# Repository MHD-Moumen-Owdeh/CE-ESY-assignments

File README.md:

# README.md files related to the assignments are in the folders

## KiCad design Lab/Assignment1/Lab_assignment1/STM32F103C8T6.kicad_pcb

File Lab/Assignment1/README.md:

Here are the required files for the assignment.
I started working on the PCB design but wasn’t able to fully complete it before the deadline.
Any feedback or notes would be greatly appreciated.

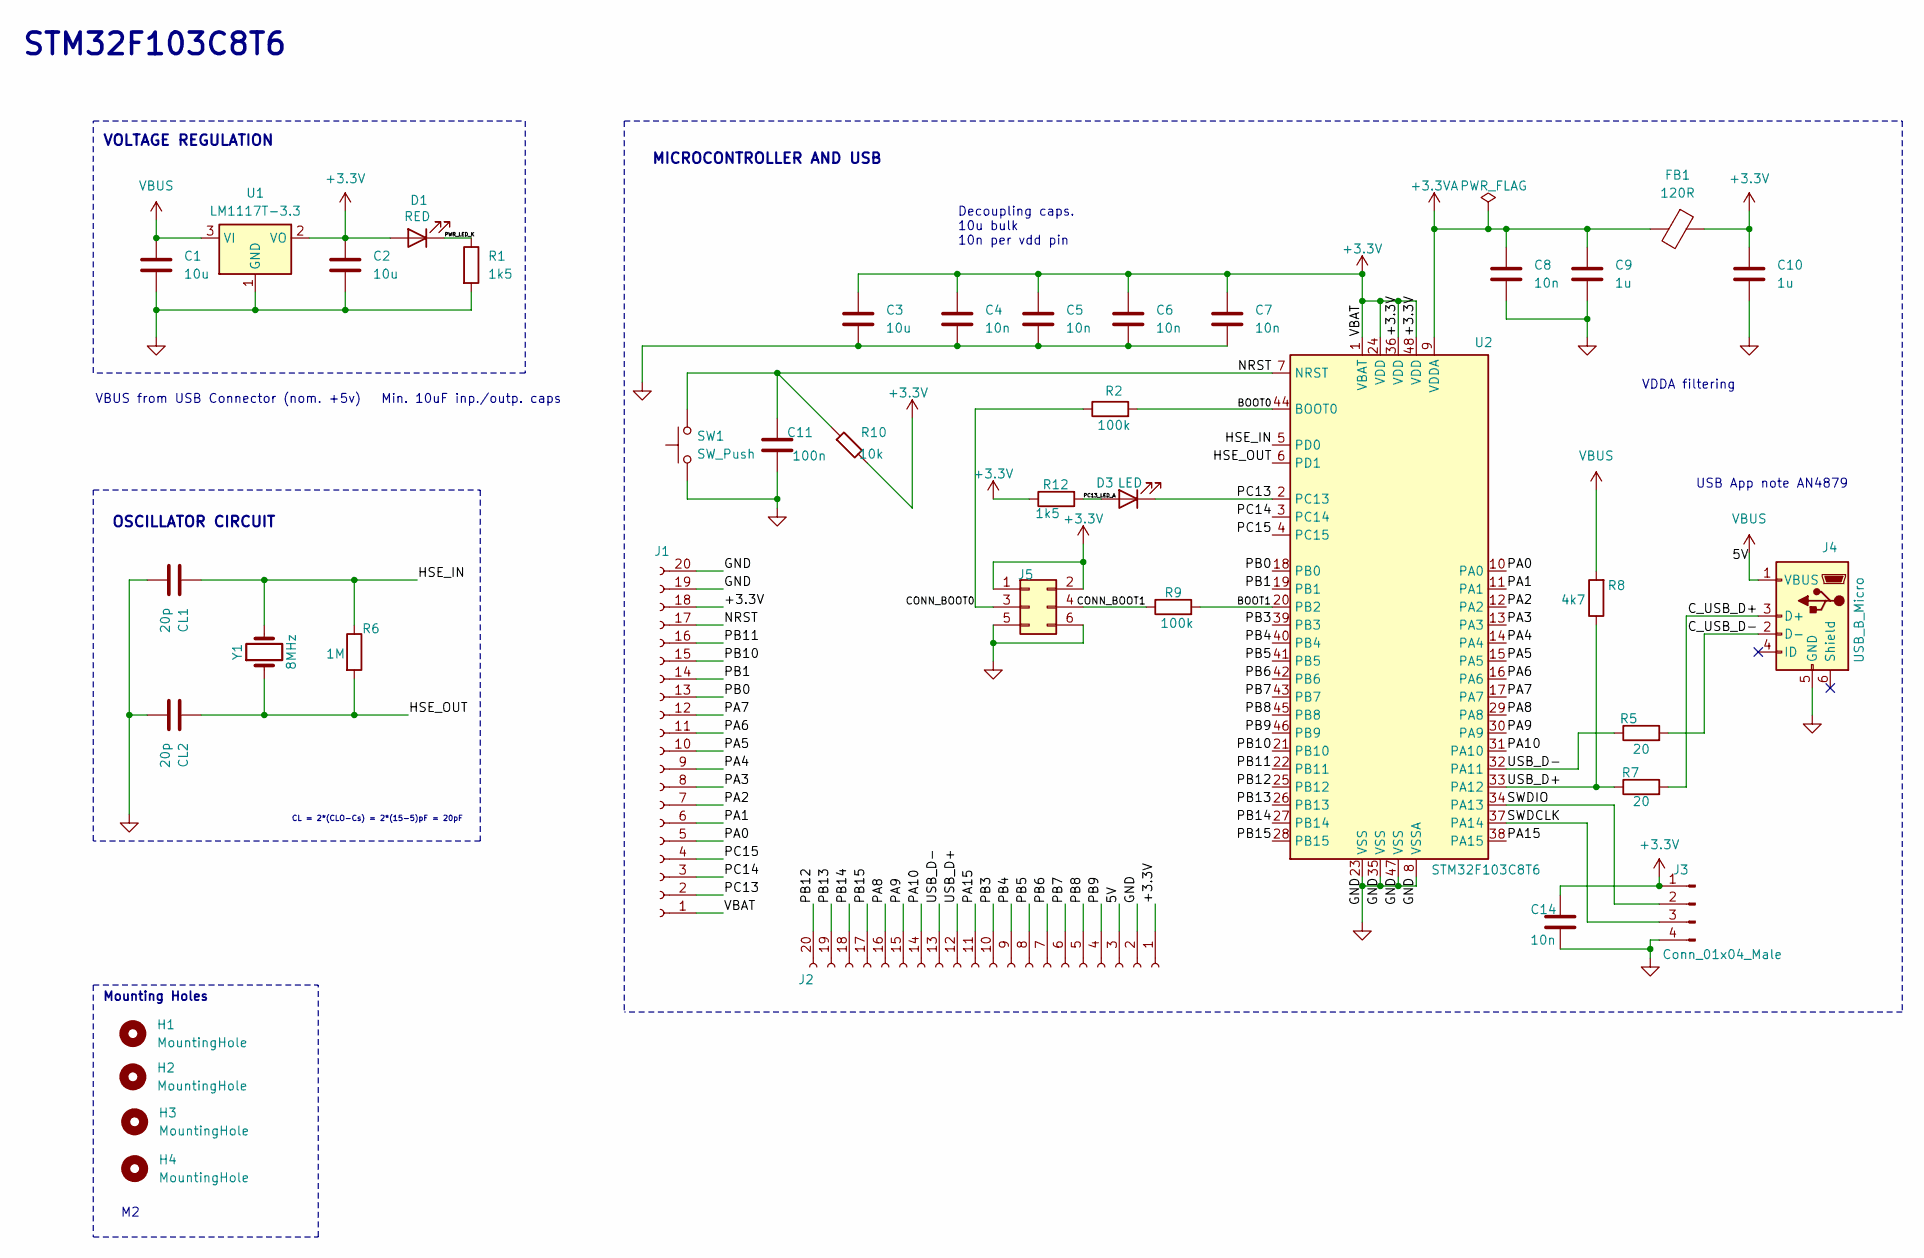
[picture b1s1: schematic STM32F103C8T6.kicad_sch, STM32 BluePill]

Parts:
C1, C2, C3: 10u; C_0603_1608Metric
C4, C5, C6, C7, C8: 10n; C_0603_1608Metric
C9, C10: 1u; C_0402_1005Metric
C11: 100n; C_0402_1005Metric
C14: 10n; C_0402_1005Metric
CL1, CL2: 20p; C_0402_1005Metric
D1: RED; LED_0603_1608Metric
D3: LED; LED_0603_1608Metric
FB1: 120R; L_0603_1608Metric
H1, H2, H3, H4: MountingHole; MountingHole_2.2mm_M2
J1, J2: Conn_01x20_Socket; PinSocket_1x20_P2.00mm_Vertical
J3: Conn_01x04_Male; PinHeader_1x04_P2.00mm_Vertical
J4: USB_B_Micro; USB_Micro-B_Wuerth_629105150521
J5: Conn_02x03_Odd_Even; PinHeader_2x03_P2.54mm_Vertical
R1, R12: 1k5; R_0402_1005Metric
R2, R9: 100k; R_0402_1005Metric
R5, R7: 20; R_01005_0402Metric
R6: 1M; R_0603_1608Metric
R8: 4k7; R_0402_1005Metric
R10: 10k; R_0402_1005Metric
SW1: SW_Push; SW_Push_1P1T_NO_CK_KMR2
U1: LM1117T-3.3; TO-220-3_Vertical
U2: STM32F103C8T6; LQFP-48_7x7mm_P0.5mm
Y1: 8MHz; Crystal_SMD_5032-2Pin_5.0x3.2mm_HandSoldering

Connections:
+3.3V: C2.1, C3.1, C4.1, C5.1, C6.1, C7.1, C10.1, C14.1, D1.2 (A), FB1.1, J1.1, J1.18, J2.1, J3.1, J5.1, J5.2, R10.2, R12.1, U1.2 (VO), U2.1 (VBAT), U2.24 (VDD), U2.36 (VDD), U2.48 (VDD)
+3.3VA: C8.1, C9.1, FB1.2, U2.9 (VDDA)
/BOOT0: R2.2, U2.44 (BOOT0)
/BOOT1: R9.2, U2.20 (PB2)
/CONN_BOOT0: J5.3, R2.1
/CONN_BOOT1: J5.4, R9.1
/C_USB_D+: J4.3 (D+), R7.2
/C_USB_D-: J4.2 (D-), R5.2
/HSE_IN: CL1.1, R6.1, U2.5 (PD0), Y1.2
/HSE_OUT: CL2.1, R6.2, U2.6 (PD1), Y1.1
/NRST: C11.1, J1.17, R10.1, SW1.2, U2.7 (NRST)
/PA0: J1.5, U2.10 (PA0)
/PA1: J1.6, U2.11 (PA1)
/PA2: J1.7, U2.12 (PA2)
/PA3: J1.8, U2.13 (PA3)
/PA4: J1.9, U2.14 (PA4)
/PA5: J1.10, U2.15 (PA5)
/PA6: J1.11, U2.16 (PA6)
/PA7: J1.12, U2.17 (PA7)
/PA8: J2.16, U2.29 (PA8)
/PA9: J2.15, U2.30 (PA9)
/PA10: J2.14, U2.31 (PA10)
/PA15: J2.11, U2.38 (PA15)
/PB0: J1.13, U2.18 (PB0)
/PB1: J1.14, U2.19 (PB1)
/PB3: J2.10, U2.39 (PB3)
/PB4: J2.9, U2.40 (PB4)
/PB5: J2.8, U2.41 (PB5)
/PB6: J2.7, U2.42 (PB6)
/PB7: J2.6, U2.43 (PB7)
/PB8: J2.5, U2.45 (PB8)
/PB9: J2.4, U2.46 (PB9)
/PB10: J1.15, U2.21 (PB10)
/PB11: J1.16, U2.22 (PB11)
/PB12: J2.20, U2.25 (PB12)
/PB13: J2.19, U2.26 (PB13)
/PB14: J2.18, U2.27 (PB14)
/PB15: J2.17, U2.28 (PB15)
/PC13: D3.1 (K), J1.2, U2.2 (PC13)
/PC13_LED_A: D3.2 (A), R12.2
/PC14: J1.3, U2.3 (PC14)
/PC15: J1.4, U2.4 (PC15)
/PWR_LED_K: D1.1 (K), R1.1
/SWDCLK: J3.3, U2.37 (PA14)
/SWDIO: J3.2, U2.34 (PA13)
/USB_D+: J2.12, R7.1, R8.1, U2.33 (PA12)
/USB_D-: J2.13, R5.1, U2.32 (PA11)
GND: C1.2, C2.2, C3.2, C4.2, C5.2, C6.2, C7.2, C8.2, C9.2, C10.2, C11.2, C14.2, CL1.2, CL2.2, J1.19, J1.20, J2.2, J3.4, J4.5 (GND), J5.5, J5.6, R1.2, SW1.1, U1.1 (GND), U2.8 (VSSA), U2.23 (VSS), U2.35 (VSS), U2.47 (VSS)
VBUS: C1.1, J2.3, J4.1 (VBUS), R8.2, U1.3 (VI)

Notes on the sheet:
VDDA filtering
MICROCONTROLLER AND USB
Min. 10uF inp./outp. caps
Mounting Holes
VBUS from USB Connector (nom. +5v)
VOLTAGE REGULATION
CL = 2*(CLO-Cs) = 2*(15-5)pF = 20pF
USB App note AN4879
Decoupling caps. 10u bulk 10n per vdd pin
OSCILLATOR CIRCUIT
STM32F103C8T6

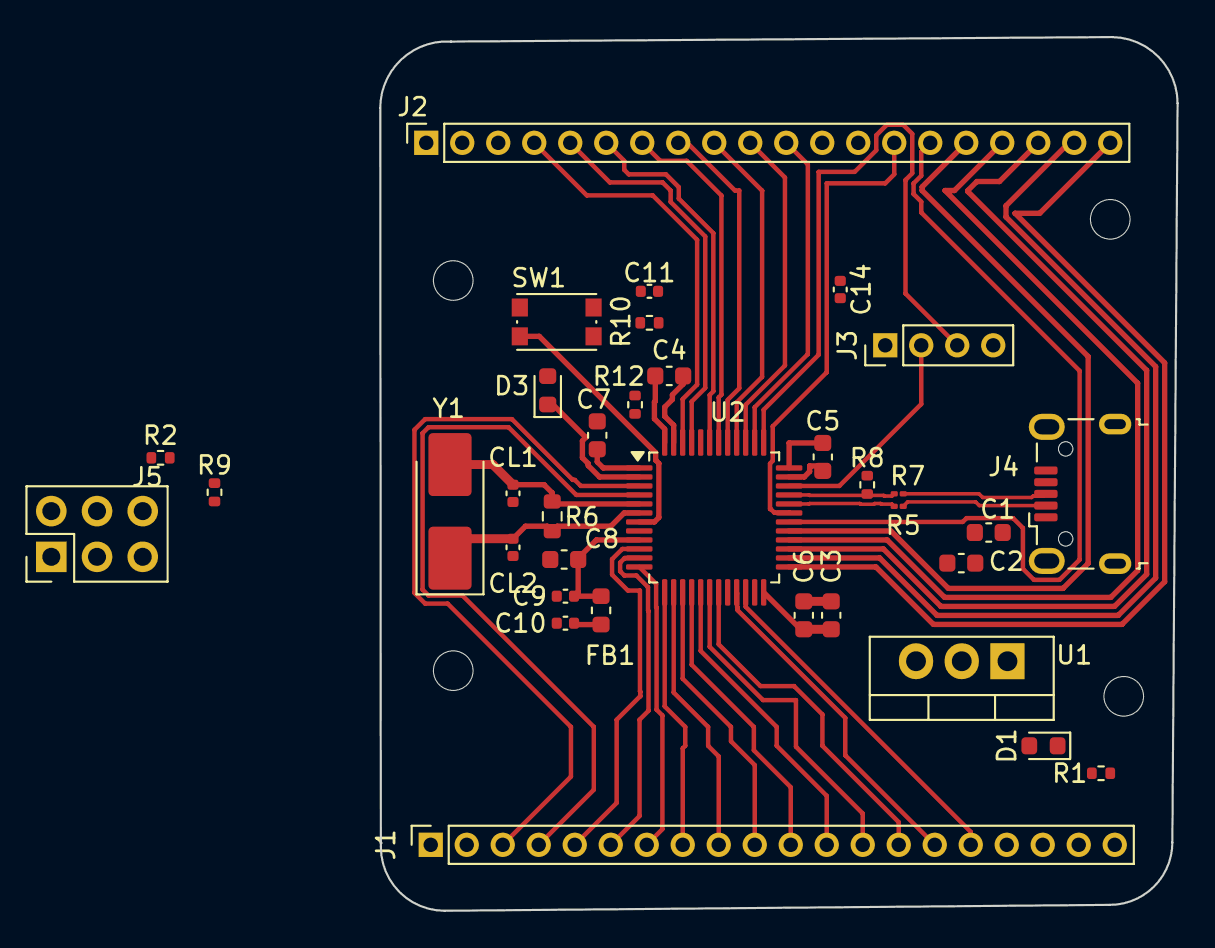
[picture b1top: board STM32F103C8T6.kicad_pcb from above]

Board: 2 copper layers, 44.3 x 48.5 mm, 39 parts (0 on the bottom side), 49 nets.

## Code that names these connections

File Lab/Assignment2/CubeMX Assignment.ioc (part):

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Mcu.Name=STM32F103C(8-B)Tx
Mcu.Package=LQFP48
Mcu.UserName=STM32F103C8Tx
PA0-WKUP.Signal=GPIO_Input
PA1.Signal=GPIO_Output
PA10.Signal=GPIO_Output
PA11.Signal=GPIO_Output
PA12.GPIOParameters=GPIO_Label
PA12.GPIO_Label=MOTOR_CTRL
PA12.Signal=GPIO_Output
PA13.Mode=Serial_Wire
PA13.Signal=SYS_JTMS-SWDIO
PA14.Mode=Serial_Wire
PA14.Signal=SYS_JTCK-SWCLK
PA15.Signal=GPIO_Output
PA2.Signal=GPIO_Input
PA3.Signal=GPIO_Input
PA4.Signal=GPIO_Input
PA5.Signal=GPIO_Input
PA6.Signal=GPIO_Input
PA7.Signal=GPIO_Input
PA8.Signal=GPIO_Output
PA9.Signal=GPIO_Output
PB0.Signal=GPIO_Input
PB1.Signal=GPIO_Input
PB10.GPIOParameters=GPIO_Label
PB10.GPIO_Label=TC74_1_SCL
PB10.Mode=I2C
PB10.Signal=I2C2_SCL
PB11.GPIOParameters=GPIO_Label
PB11.GPIO_Label=TC74_1_SDA
PB11.Mode=I2C
PB11.Signal=I2C2_SDA
PB12.Signal=GPIO_Input
PB13.Signal=GPIO_Output
PB14.Signal=GPIO_Output
PB15.Signal=GPIO_Output
PB2.Signal=GPIO_Input
PB3.Signal=GPIO_Output
PB4.Signal=S_TIM3_CH1
PB5.Signal=GPIO_Output
PB6.Signal=GPIO_Output
PB7.Signal=GPIO_Output
PB8.Signal=GPIO_Output
PB9.Signal=GPIO_Output
PC13-TAMPER-RTC.GPIOParameters=GPIO_PuPd,GPIO_Label
PC13-TAMPER-RTC.GPIO_Label=BTN_1
PC13-TAMPER-RTC.GPIO_PuPd=GPIO_PULLUP
PC13-TAMPER-RTC.Signal=GPIO_Input
PC13-TAMPER-RTC.Stacked=true
PC14-OSC32_IN.GPIOParameters=GPIO_PuPd,GPIO_Label
PC14-OSC32_IN.GPIO_Label=BTN_2
PC14-OSC32_IN.GPIO_PuPd=GPIO_PULLUP
PC14-OSC32_IN.Signal=GPIO_Input
PC14-OSC32_IN.Stacked=true
PC15-OSC32_OUT.GPIOParameters=GPIO_PuPd,GPIO_Label
PC15-OSC32_OUT.GPIO_Label=BTN_3
PC15-OSC32_OUT.GPIO_PuPd=GPIO_PULLUP
PC15-OSC32_OUT.Signal=GPIO_Input
PC15-OSC32_OUT.Stacked=true
PD0-OSC_IN.Mode=HSE-External-Oscillator
PD0-OSC_IN.Signal=RCC_OSC_IN
PD1-OSC_OUT.Mode=HSE-External-Oscillator
PD1-OSC_OUT.Signal=RCC_OSC_OUT
RCC.SYSCLKFreq_VALUE=72000000
RCC.SYSCLKSource=RCC_SYSCLKSOURCE_PLLCLK
board=custom

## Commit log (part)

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2026-04-30 Rename README.md to README1.md
2026-05-25 Create Lab/Assignment1
2026-05-25 README for Assignment 1
2026-05-25 Add LABREADME.md with information reference
